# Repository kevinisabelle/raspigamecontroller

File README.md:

# RaspberryPi Bluetooth LE HID Game controller

## Reference documentation

- _HID Usage Table_: https://www.usb.org/document-library/hid-usage-tables-16
- _Device Class Definition for Human Interface Devices (HID)_: https://www.usb.org/document-library/device-class-definition-hid-111
- _HID over GATT Profile 1.0_: https://www.bluetooth.com/specifications/specs/hid-over-gatt-profile-1-0/
- _Bluez dbus interfaces_: https://github.com/bluez/bluez/tree/master/doc

## Current Issues:

- Reconnection not working automatically
- The number of axies also seems to be limited.

## Setup

### Install python and bluez

```bash
#sudo apt get py3-setuptools
sudo apt update && sudo apt upgrade -y
sudo apt install libbluetooth-dev

# Blutooth
sudo systemctl enable bluetooth
sudo systemctl start bluetooth
```

### Enable Spi0 and Spi1

- Run the raspi-config app and enable Interface Spi.
- Then modify /boot/firmware/config.txt
- Add these if not present:

```
dtparam=spi=on
dtoverlay=spi1-3cs
```

- Reboot

### Setup bluez service parameters

```bash
sudo nano /lib/systemd/system/bluetooth.service

# Modify the exec start
ExecStart=/usr/libexec/bluetooth/bluetoothd -E --noplugin=*

# Save the file and restart bluetooth

sudo systemctl daemon-reload
sudo systemctl restart bluetooth
```

### Generating the Hid Report Map and Payload Interface

In the HidTools folder, use the HidReportMapCreator program.

- Create a copy of the KiGPSimple.cs class and name it as you like
- Modify the Program.cs and use the new class to create the device reference
- Run the program
- Copy the python code from the output in the python/GamepadValues.py file
- Modify the python/UpdaterService.py and adapt the \_update_gamepad_controls according to the generated GamepadValues1 class

## Running

### Start the program

- Copy the content of the python folder on the Pi
- Run with

```bash
sudo python3 App.py
```

- Once the program is properly started, you can connect it to Windows using the Bluetooth configuration like any device.
- Once the device is bonded in Windows, you can open the "Set up USB controller" to display connected Gamepads.

## Debugging

### Using dbus-tool

Use dbus-tool to check Bluez is connecting with the program properly:

```

sudo dbus-monitor --system

```

### Using Wireshark

Use Wireshark on Windows to inspect the GATT services packets.

- Start a session using Pcap2
- Filter out protocol USB

```

!(\_ws.col.protocol == "USB")

```

- Or you can filter in the proper services:

```

(\_ws.col.protocol == "ATT" || \_ws.col.protocol == "SDP" || \_ws.col.protocol == "SMP" || \_ws.col.protocol == "GAP" || \_ws.col.protocol == "GATT" || \_ws.col.protocol == "HCI_EVT")

```

### Using Hid Explorer

You can also use this great online tool (which runs in the browser): https://nondebug.github.io/webhid-explorer/ . Using this tool you can connect to the recognized HID devices and see their definition and notifications.

## Hid Creator output example:

```
Hid Report Map and Payload interface creator
---------------------------------------------------

Notes:
-------
1. This tool is used to generate a report map and payload for a HID device.
2. The report map is a list of instructions that the device uses to send data to the host.
3. It will generate the Python class code for the report payload to use in the python part of this project.

---------------------
Report Map Descriptor
---------------------

0x05, 0x01      # Usage Page (Generic Desktop Controls)
0x09, 0x05      # Usage (Gamepad)
0xA1, 0x01      # Collection (Application)
0x85, 0x01      # Report ID 1
0x05, 0x09      # Usage Page (Button)
0x19, 0x01      # Usage Minimum (1)
0x29, 0x08      # Usage Maximum (8)
0x15, 0x00      # Logical Minimum (0)
0x25, 0x01      # Logical Maximum (1)
0x75, 0x01      # Report Size (1)
0x95, 0x08      # Report Count (8)
0x81, 0x02      # Input (00000010)
0x05, 0x01      # Usage Page (Generic Desktop Controls)
0x09, 0x36      # Usage (Slider)
0x19, 0x01      # Usage Minimum (1)
0x29, 0x01      # Usage Maximum (1)
0x15, 0x00      # Logical Minimum (0)
0x25, 0xFF      # Logical Maximum (255)
0x75, 0x08      # Report Size (8)
0x95, 0x01      # Report Count (1)
0x81, 0x02      # Input (00000010)
0x05, 0x01      # Usage Page (Generic Desktop Controls)
0x09, 0x36      # Usage (Slider)
0x19, 0x01      # Usage Minimum (1)
0x29, 0x01      # Usage Maximum (1)
0x15, 0x00      # Logical Minimum (0)
0x25, 0xFF      # Logical Maximum (255)
0x75, 0x08      # Report Size (8)
0x95, 0x01      # Report Count (1)
0x81, 0x02      # Input (00000010)
0x05, 0x01      # Usage Page (Generic Desktop Controls)
0x09, 0x36      # Usage (Slider)
0x19, 0x01      # Usage Minimum (1)
0x29, 0x01      # Usage Maximum (1)
0x15, 0x00      # Logical Minimum (0)
0x25, 0xFF      # Logical Maximum (255)
0x75, 0x08      # Report Size (8)
0x95, 0x01      # Report Count (1)
0x81, 0x02      # Input (00000010)
0xC0    # End Collection

----------------------
Report Payload Example
----------------------

Btn1 #1 (1 bits) Unspecified
Btn1 #2 (1 bits) Unspecified
Btn1 #3 (1 bits) Unspecified
Btn1 #4 (1 bits) Unspecified
Btn1 #5 (1 bits) Unspecified
Btn1 #6 (1 bits) Unspecified
Btn1 #7 (1 bits) Unspecified
Btn1 #8 (1 bits) Unspecified
Slider #1 (8 bits) Slider
Slider2 #1 (8 bits) Slider
Slider3 #1 (8 bits) Slider

----------------------------------
Report Payload Example (Formatted)
----------------------------------

BBBBBBBB SSSSSSSS SSSSSSSS SSSSSSSS
12345678 11111111 11111111 11111111

------------
Python class
------------

class GamepadValues1:
    def __init__(self, Btn10=0, Btn11=0, Btn12=0, Btn13=0, Btn14=0, Btn15=0, Btn16=0, Btn17=0, Slider0=0, Slider20=0, Slider30=0):
        self.Btn10 = Btn10 & 0x1
        self.Btn11 = Btn11 & 0x1
        self.Btn12 = Btn12 & 0x1
        self.Btn13 = Btn13 & 0x1
        self.Btn14 = Btn14 & 0x1
        self.Btn15 = Btn15 & 0x1
        self.Btn16 = Btn16 & 0x1
        self.Btn17 = Btn17 & 0x1
        self.Slider0 = Slider0 & 0xFF
        self.Slider20 = Slider20 & 0xFF
        self.Slider30 = Slider30 & 0xFF

    def set_Btn10(self, value):
        self.Btn10 = value & 0x1

    def set_Btn11(self, value):
        self.Btn11 = value & 0x1

    def set_Btn12(self, value):
        self.Btn12 = value & 0x1

    def set_Btn13(self, value):
        self.Btn13 = value & 0x1

    def set_Btn14(self, value):
        self.Btn14 = value & 0x1

    def set_Btn15(self, value):
        self.Btn15 = value & 0x1

    def set_Btn16(self, value):
        self.Btn16 = value & 0x1

    def set_Btn17(self, value):
        self.Btn17 = value & 0x1

    def set_Slider0(self, value):
        self.Slider0 = value & 0xFF

    def set_Slider20(self, value):
        self.Slider20 = value & 0xFF

    def set_Slider30(self, value):
        self.Slider30 = value & 0xFF

    def get_report(self):
        total = 0
        total = (total << 1) | self.Btn10
        total = (total << 1) | self.Btn11
        total = (total << 1) | self.Btn12
        total = (total << 1) | self.Btn13
        total = (total << 1) | self.Btn14
        total = (total << 1) | self.Btn15
        total = (total << 1) | self.Btn16
        total = (total << 1) | self.Btn17
        total = (total << 8) | self.Slider0
        total = (total << 8) | self.Slider20
        total = (total << 8) | self.Slider30
        result = total.to_bytes(4, byteorder='big')
        return bytes([0x01] + list(result))

    def get_report_map(self):
        return bytes([
            0x05, 0x01,   # Usage Page (Generic Desktop Controls)
            0x09, 0x05,   # Usage (Gamepad)
            0xA1, 0x01,   # Collection (Application)
            0x85, 0x01,   # Report ID 1
            0x05, 0x09,   # Usage Page (Button)
            0x19, 0x01,   # Usage Minimum (1)
            0x29, 0x08,   # Usage Maximum (8)
            0x15, 0x00,   # Logical Minimum (0)
            0x25, 0x01,   # Logical Maximum (1)
            0x75, 0x01,   # Report Size (1)
            0x95, 0x08,   # Report Count (8)
            0x81, 0x02,   # Input (00000010)
            0x05, 0x01,   # Usage Page (Generic Desktop Controls)
            0x09, 0x36,   # Usage (Slider)
            0x19, 0x01,   # Usage Minimum (1)
            0x29, 0x01,   # Usage Maximum (1)
            0x15, 0x00,   # Logical Minimum (0)
            0x25, 0xFF,   # Logical Maximum (255)
            0x75, 0x08,   # Report Size (8)
            0x95, 0x01,   # Report Count (1)
            0x81, 0x02,   # Input (00000010)
            0x05, 0x01,   # Usage Page (Generic Desktop Controls)
            0x09, 0x36,   # Usage (Slider)
            0x19, 0x01,   # Usage Minimum (1)
            0x29, 0x01,   # Usage Maximum (1)
            0x15, 0x00,   # Logical Minimum (0)
            0x25, 0xFF,   # Logical Maximum (255)
            0x75, 0x08,   # Report Size (8)
            0x95, 0x01,   # Report Count (1)
            0x81, 0x02,   # Input (00000010)
            0x05, 0x01,   # Usage Page (Generic Desktop Controls)
            0x09, 0x36,   # Usage (Slider)
            0x19, 0x01,   # Usage Minimum (1)
            0x29, 0x01,   # Usage Maximum (1)
            0x15, 0x00,   # Logical Minimum (0)
            0x25, 0xFF,   # Logical Maximum (255)
            0x75, 0x08,   # Report Size (8)
            0x95, 0x01,   # Report Count (1)
            0x81, 0x02,   # Input (00000010)
            0xC0,   # End Collection
        ])

```

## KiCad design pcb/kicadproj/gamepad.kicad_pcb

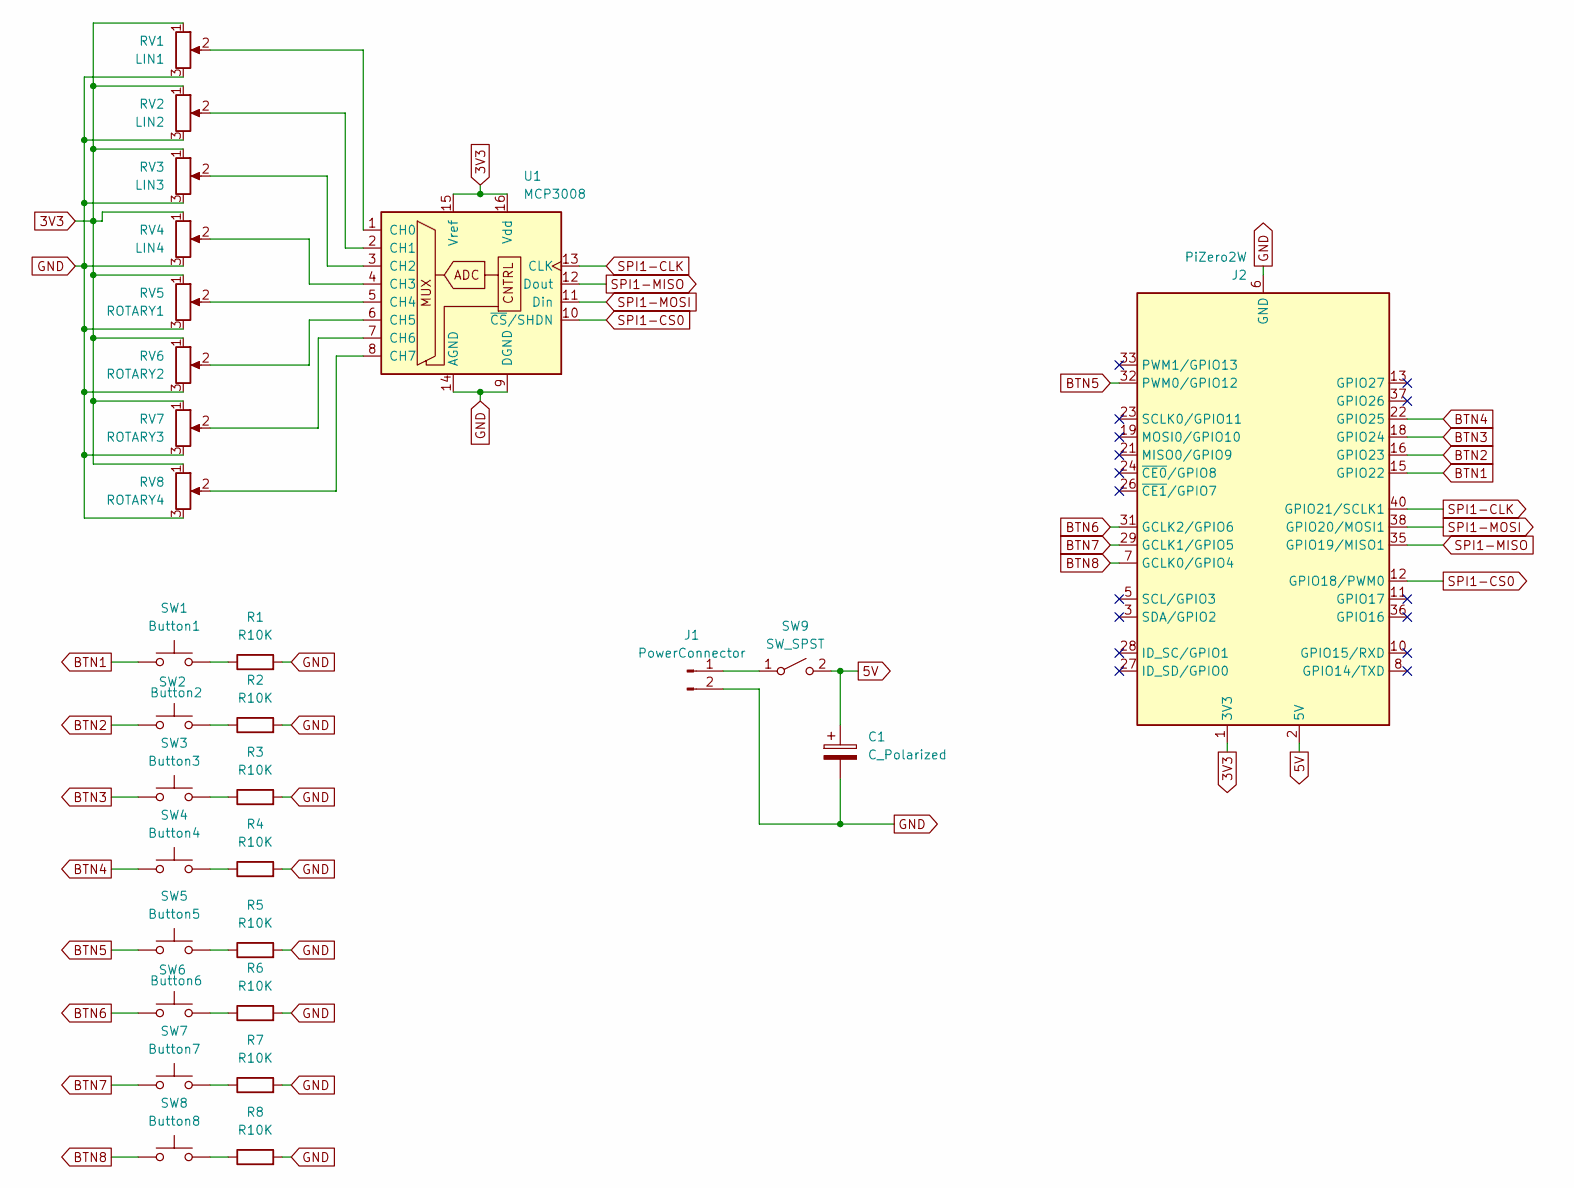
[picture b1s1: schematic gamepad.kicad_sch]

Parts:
C1: C_Polarized; CP_Radial_D4.0mm_P2.00mm
J1: PowerConnector; PinHeader_1x02_P2.54mm_Vertical
J2: PiZero2W; PinSocket_2x20_P2.54mm_Vertical
R1, R2, R3, R4, R5, R6, R7, R8: R10K; R_1206_3216Metric_Pad1.30x1.75mm_HandSolder
RV1: LIN1; Potentiometer_Bourns_PTA6043_Single_Slide
RV2: LIN2; Potentiometer_Bourns_PTA6043_Single_Slide
RV3: LIN3; Potentiometer_Bourns_PTA6043_Single_Slide
RV4: LIN4; Potentiometer_Bourns_PTA6043_Single_Slide
RV5: ROTARY1; Potentiometer_Bourns_PTV09A-1_Single_Vertical
RV6: ROTARY2; Potentiometer_Bourns_PTV09A-1_Single_Vertical
RV7: ROTARY3; Potentiometer_Bourns_PTV09A-1_Single_Vertical
RV8: ROTARY4; Potentiometer_Bourns_PTV09A-1_Single_Vertical
SW1: Button1; SW_SPST_Omron_B3F-40xx
SW2: Button2; SW_SPST_Omron_B3F-40xx
SW3: Button3; SW_SPST_Omron_B3F-40xx
SW4: Button4; SW_SPST_Omron_B3F-40xx
SW5: Button5; SW_SPST_Omron_B3F-40xx
SW6: Button6; SW_SPST_Omron_B3F-40xx
SW7: Button7; SW_SPST_Omron_B3F-40xx
SW8: Button8; SW_SPST_Omron_B3F-40xx
SW9: SW_SPST; SW_DIP_SPSTx01_Slide_9.78x4.72mm_W7.62mm_P2.54mm
U1: MCP3008; CERDIP-16_W7.62mm_SideBrazed_Socket

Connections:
3V3: J2.1 (3V3), J2.17 (3V3), RV1.1, RV2.1, RV3.1, RV4.1, RV5.1, RV6.1, RV7.1, RV8.1, U1.15 (Vref), U1.16 (Vdd)
5V: C1.1, J2.2 (5V), J2.4 (5V), SW9.2 (B)
BTN1: J2.15 (GPIO22), SW1.1
BTN2: J2.16 (GPIO23), SW2.1
BTN3: J2.18 (GPIO24), SW3.1
BTN4: J2.22 (GPIO25), SW4.1
BTN5: J2.32 (PWM0/GPIO12), SW5.1
BTN6: J2.31 (GCLK2/GPIO6), SW6.1
BTN7: J2.29 (GCLK1/GPIO5), SW7.1
BTN8: J2.7 (GCLK0/GPIO4), SW8.1
GND: C1.2, J1.2, J2.6 (GND), J2.9 (GND), J2.14 (GND), J2.20 (GND), J2.25 (GND), J2.30 (GND), J2.34 (GND), J2.39 (GND), R1.2, R2.2, R3.2, R4.2, R5.2, R6.2, R7.2, R8.2, RV1.3, RV2.3, RV3.3, RV4.3, RV5.3, RV6.3, RV7.3, RV8.3, U1.9 (DGND), U1.14 (AGND)
unnamed: J1.1, SW9.1 (A)
unnamed: R1.1, SW1.2
unnamed: R2.1, SW2.2
unnamed: R3.1, SW3.2
unnamed: R4.1, SW4.2
unnamed: R5.1, SW5.2
unnamed: R6.1, SW6.2
unnamed: R7.1, SW7.2
unnamed: R8.1, SW8.2
unnamed: RV1.2, U1.1 (CH0)
unnamed: RV2.2, U1.2 (CH1)
unnamed: RV3.2, U1.3 (CH2)
unnamed: RV4.2, U1.4 (CH3)
unnamed: RV5.2, U1.5 (CH4)
unnamed: RV6.2, U1.6 (CH5)
unnamed: RV7.2, U1.7 (CH6)
unnamed: RV8.2, U1.8 (CH7)
SPI1-CLK: J2.40 (GPIO21/SCLK1), U1.13 (CLK)
SPI1-CS0: J2.12 (GPIO18/PWM0), U1.10 (~CS/SHDN)
SPI1-MISO: J2.35 (GPIO19/MISO1), U1.12 (Dout)
SPI1-MOSI: J2.38 (GPIO20/MOSI1), U1.11 (Din)

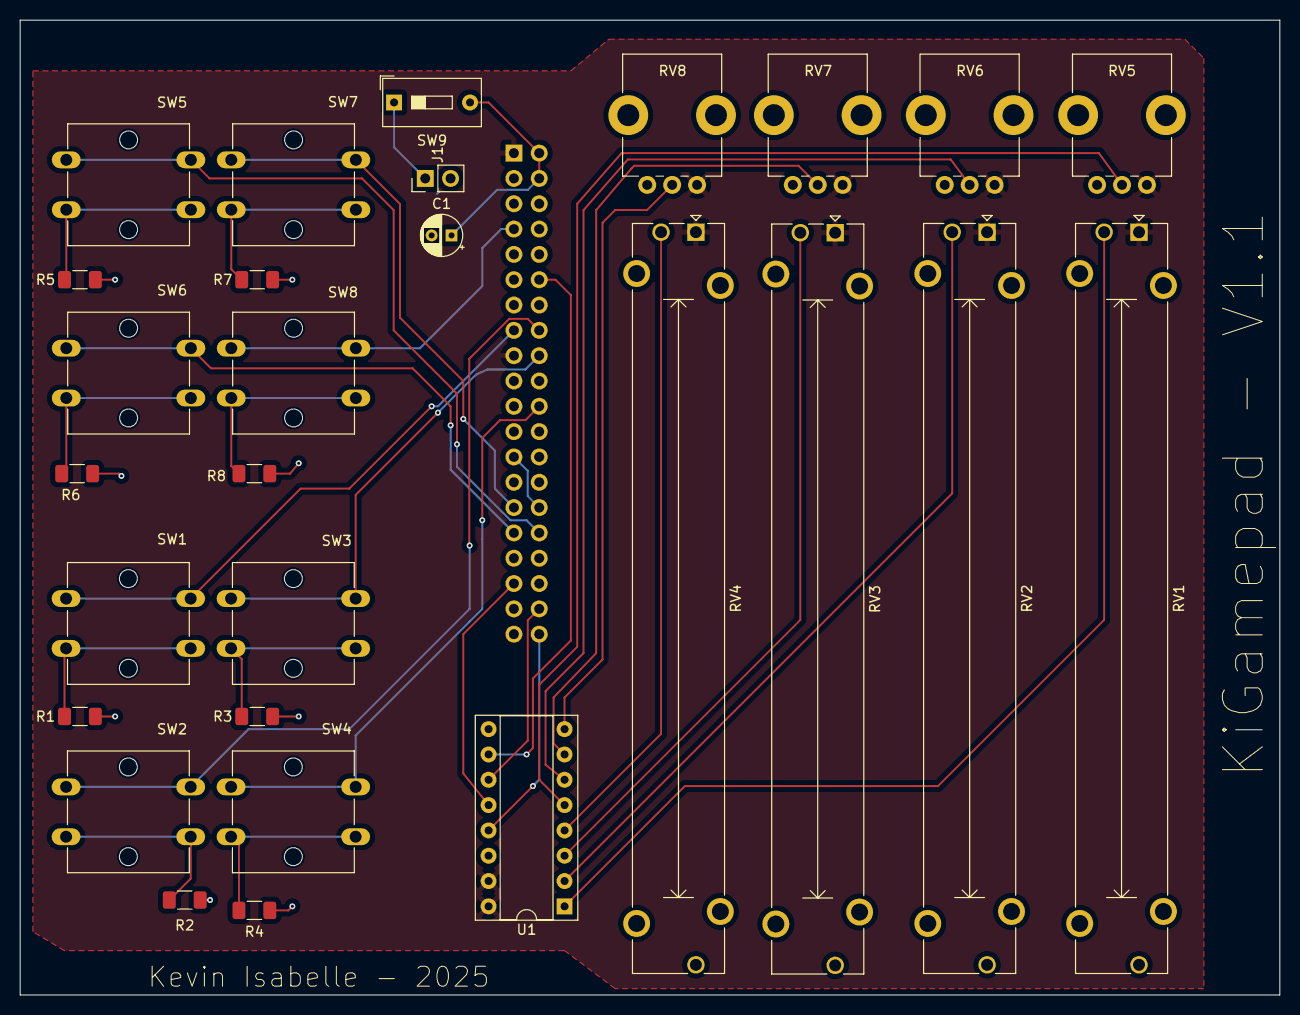
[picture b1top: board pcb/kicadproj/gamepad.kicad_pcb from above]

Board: 2 copper layers, 126.4 x 97.8 mm, 29 parts (1 on the bottom side), 32 nets.

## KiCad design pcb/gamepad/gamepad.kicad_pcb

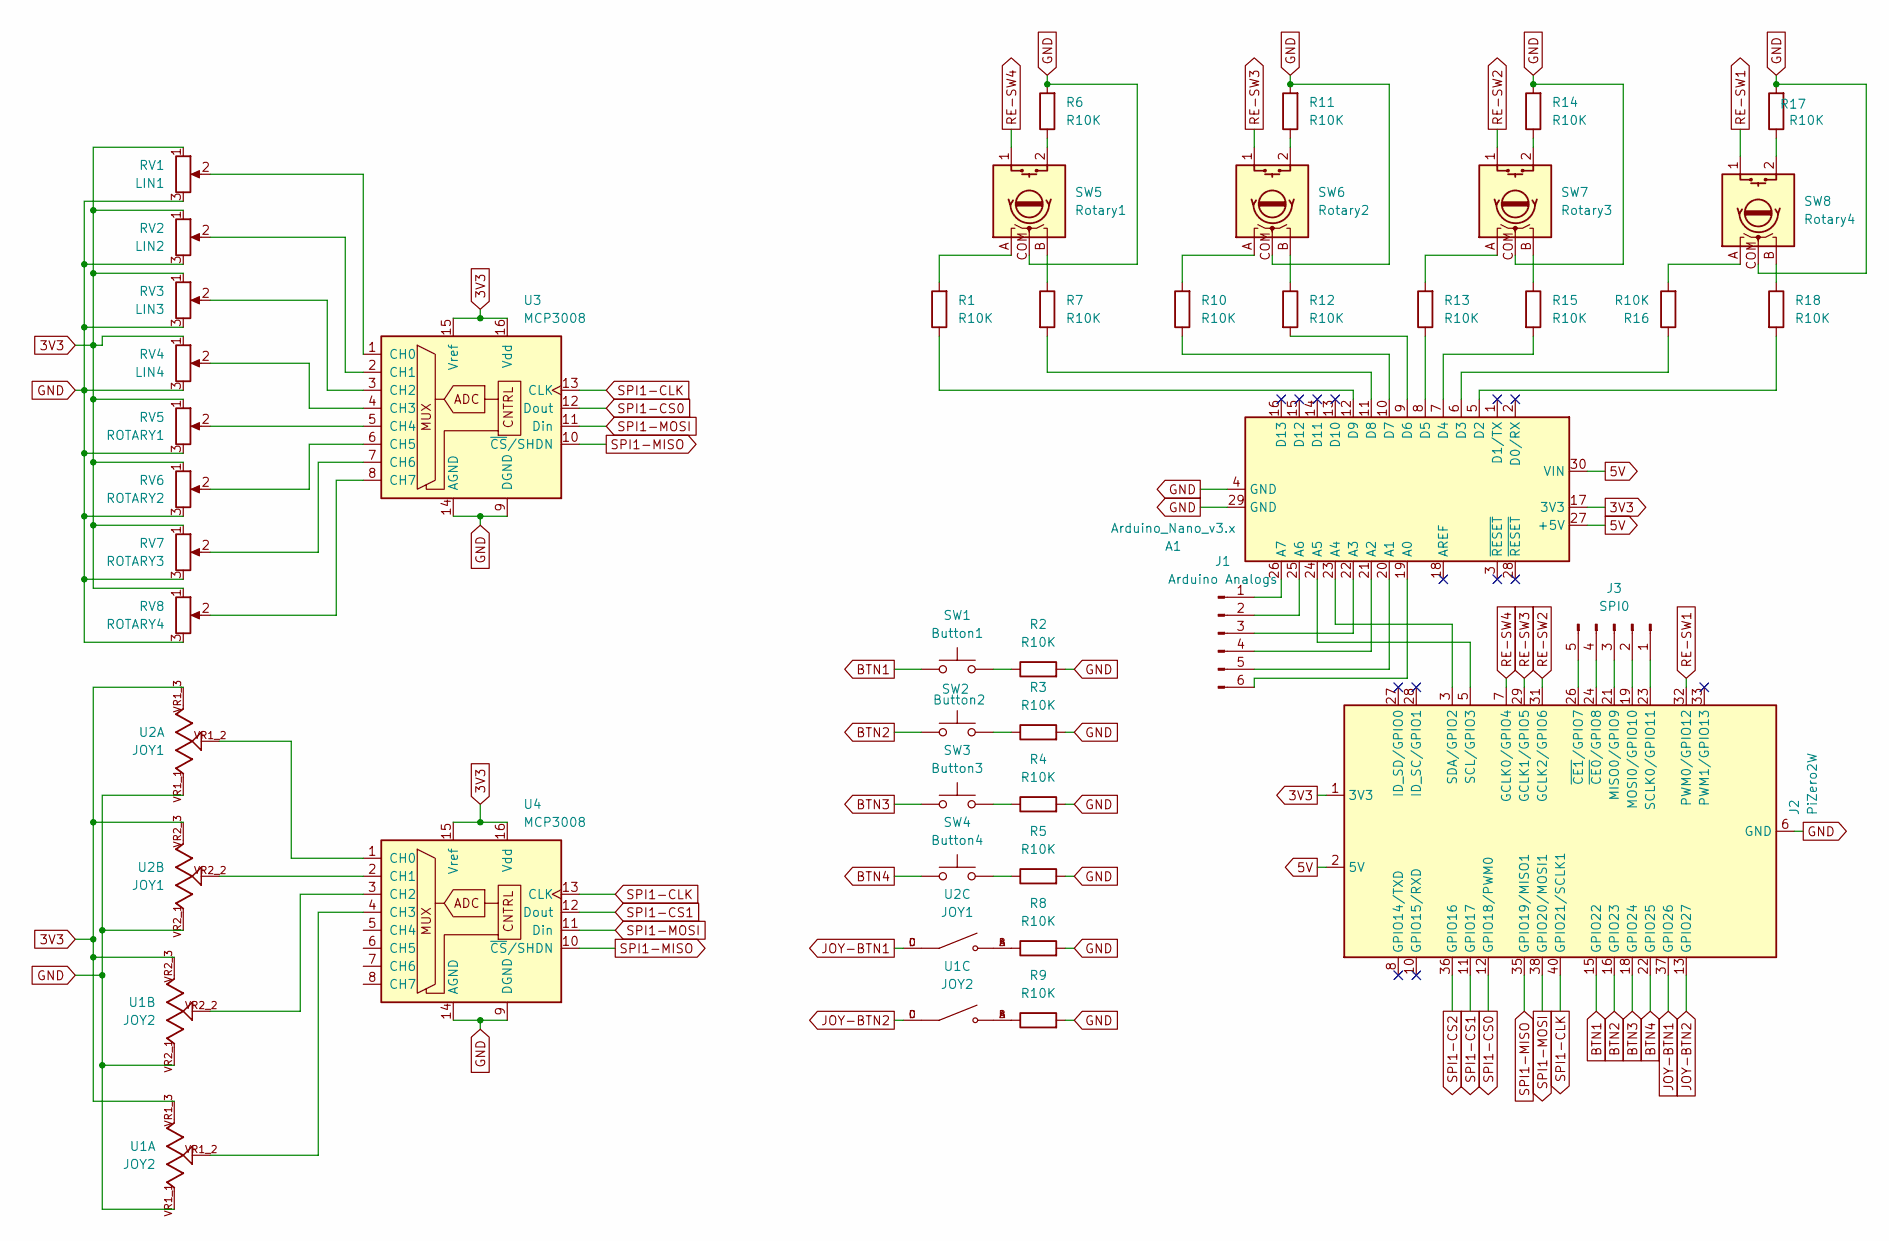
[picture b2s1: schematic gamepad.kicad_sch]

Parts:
A1: Arduino_Nano_v3.x; Arduino_Nano
J1: Arduino Analogs; PinSocket_1x05_P2.54mm_Vertical
J2: PiZero2W; PinSocket_2x20_P2.54mm_Vertical
J3: SPI0; PinSocket_1x05_P2.54mm_Vertical
R1, R2, R3, R4, R5, R6, R7, R8, R9, R10, R11, R12, R13, R14, R15, R16, R17, R18: R10K; R_1206_3216Metric_Pad1.30x1.75mm_HandSolder
RV1: LIN1; Potentiometer_Bourns_PTA6043_Single_Slide
RV2: LIN2; Potentiometer_Bourns_PTA6043_Single_Slide
RV3: LIN3; Potentiometer_Bourns_PTA4543_Single_Slide
RV4: LIN4; Potentiometer_Bourns_PTA4543_Single_Slide
RV5: ROTARY1; Potentiometer_Bourns_PTV09A-1_Single_Vertical
RV6: ROTARY2; Potentiometer_Bourns_PTV09A-1_Single_Vertical
RV7: ROTARY3; Potentiometer_Bourns_PTV09A-1_Single_Vertical
RV8: ROTARY4; Potentiometer_Bourns_PTV09A-1_Single_Vertical
SW1: Button1; SW_SPST_Omron_B3F-40xx
SW2: Button2; SW_SPST_Omron_B3F-40xx
SW3: Button3; SW_SPST_Omron_B3F-40xx
SW4: Button4; SW_SPST_Omron_B3F-40xx
SW5: Rotary1; PEC11R-4215F-S0024
SW6: Rotary2; PEC11R-4215F-S0024
SW7: Rotary3; PEC11R-4215F-S0024
SW8: Rotary4; PEC11R-4215F-S0024
U1: JOY2; CNK_THB001P; PARTREV 27 Jan 22; DigiKey_Part_Number 108-THB001P-ND
U2: JOY1; CNK_THB001P; PARTREV 27 Jan 22; DigiKey_Part_Number 108-THB001P-ND
U3, U4: MCP3008; CERDIP-16_W7.62mm_SideBrazed_Socket

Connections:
3V3: A1.17 (3V3), J2.1 (3V3), J2.17 (3V3), RV1.1, RV2.1, RV3.1, RV4.1, RV5.1, RV6.1, RV7.1, RV8.1, U1.VR1_3, U1.VR2_3, U2.VR1_3, U2.VR2_3, U3.15 (Vref), U3.16 (Vdd), U4.15 (Vref), U4.16 (Vdd)
5V: A1.27 (+5V), A1.30 (VIN), J2.2 (5V), J2.4 (5V)
BTN1: J2.15 (GPIO22), SW1.1
BTN2: J2.16 (GPIO23), SW2.1
BTN3: J2.18 (GPIO24), SW3.1
BTN4: J2.22 (GPIO25), SW4.1
GND: A1.4 (GND), A1.29 (GND), J2.6 (GND), J2.9 (GND), J2.14 (GND), J2.20 (GND), J2.25 (GND), J2.30 (GND), J2.34 (GND), J2.39 (GND), R2.2, R3.2, R4.2, R5.2, R6.2, R8.2, R9.2, R11.2, R14.2, R17.2, RV1.3, RV2.3, RV3.3, RV4.3, RV5.3, RV6.3, RV7.3, RV8.3, SW5.COM (Com), SW6.COM (Com), SW7.COM (Com), SW8.COM (Com), U1.VR1_1, U1.VR2_1, U2.VR1_1, U2.VR2_1, U3.9 (DGND), U3.14 (AGND), U4.9 (DGND), U4.14 (AGND)
JOY-BTN1: J2.37 (GPIO26), U2.C, U2.D
JOY-BTN2: J2.13 (GPIO27), U1.C, U1.D
unnamed: A1.19 (A0), J1.6
unnamed: A1.20 (A1), J1.5
unnamed: A1.21 (A2), J1.4
unnamed: A1.22 (A3), J1.3
unnamed: A1.23 (A4), J2.3 (SDA/GPIO2)
unnamed: A1.24 (A5), J2.5 (SCL/GPIO3)
unnamed: A1.25 (A6), J1.2
unnamed: A1.26 (A7), J1.1
unnamed: A1.5 (D2), R18.2
unnamed: A1.6 (D3), R16.1
unnamed: A1.7 (D4), R15.2
unnamed: A1.8 (D5), R13.1
unnamed: A1.9 (D6), R12.2
unnamed: A1.10 (D7), R10.1
unnamed: A1.11 (D8), R7.2
unnamed: A1.12 (D9), R1.1
unnamed: J2.21 (MISO0/GPIO9), J3.3
unnamed: J2.19 (MOSI0/GPIO10), J3.2
unnamed: J2.23 (SCLK0/GPIO11), J3.1
unnamed: J2.24 (~CE0/GPIO8), J3.4
unnamed: J2.26 (~CE1/GPIO7), J3.5
unnamed: R1.2, SW5.A
unnamed: R2.1, SW1.2
unnamed: R3.1, SW2.2
unnamed: R4.1, SW3.2
unnamed: R5.1, SW4.2
unnamed: R6.1, SW5.2
unnamed: R7.1, SW5.B
unnamed: R8.1, U2.A, U2.B
unnamed: R9.1, U1.A, U1.B
unnamed: R10.2, SW6.A
unnamed: R11.1, SW6.2
unnamed: R12.1, SW6.B
unnamed: R13.2, SW7.A
unnamed: R14.1, SW7.2
unnamed: R15.1, SW7.B
unnamed: R16.2, SW8.A
unnamed: R17.1, SW8.2
unnamed: R18.1, SW8.B
unnamed: RV1.2, U3.1 (CH0)
unnamed: RV2.2, U3.2 (CH1)
unnamed: RV3.2, U3.3 (CH2)
unnamed: RV4.2, U3.4 (CH3)
unnamed: RV5.2, U3.5 (CH4)
unnamed: RV6.2, U3.6 (CH5)
unnamed: RV7.2, U3.7 (CH6)
unnamed: RV8.2, U3.8 (CH7)
unnamed: U2.VR1_2, U4.1 (CH0)
unnamed: U2.VR2_2, U4.2 (CH1)
unnamed: U1.VR2_2, U4.3 (CH2)
unnamed: U1.VR1_2, U4.4 (CH3)
RE-SW1: J2.32 (PWM0/GPIO12), SW8.1
RE-SW2: J2.31 (GCLK2/GPIO6), SW7.1
RE-SW3: J2.29 (GCLK1/GPIO5), SW6.1
RE-SW4: J2.7 (GCLK0/GPIO4), SW5.1
SPI1-CLK: J2.40 (GPIO21/SCLK1), U3.13 (CLK), U4.13 (CLK)
SPI1-CS0: J2.12 (GPIO18/PWM0), U3.12 (Dout)
SPI1-CS1: J2.11 (GPIO17), U4.12 (Dout)
SPI1-CS2: J2.36 (GPIO16)
SPI1-MISO: J2.35 (GPIO19/MISO1), U3.10 (~CS/SHDN), U4.10 (~CS/SHDN)
SPI1-MOSI: J2.38 (GPIO20/MOSI1), U3.11 (Din), U4.11 (Din)

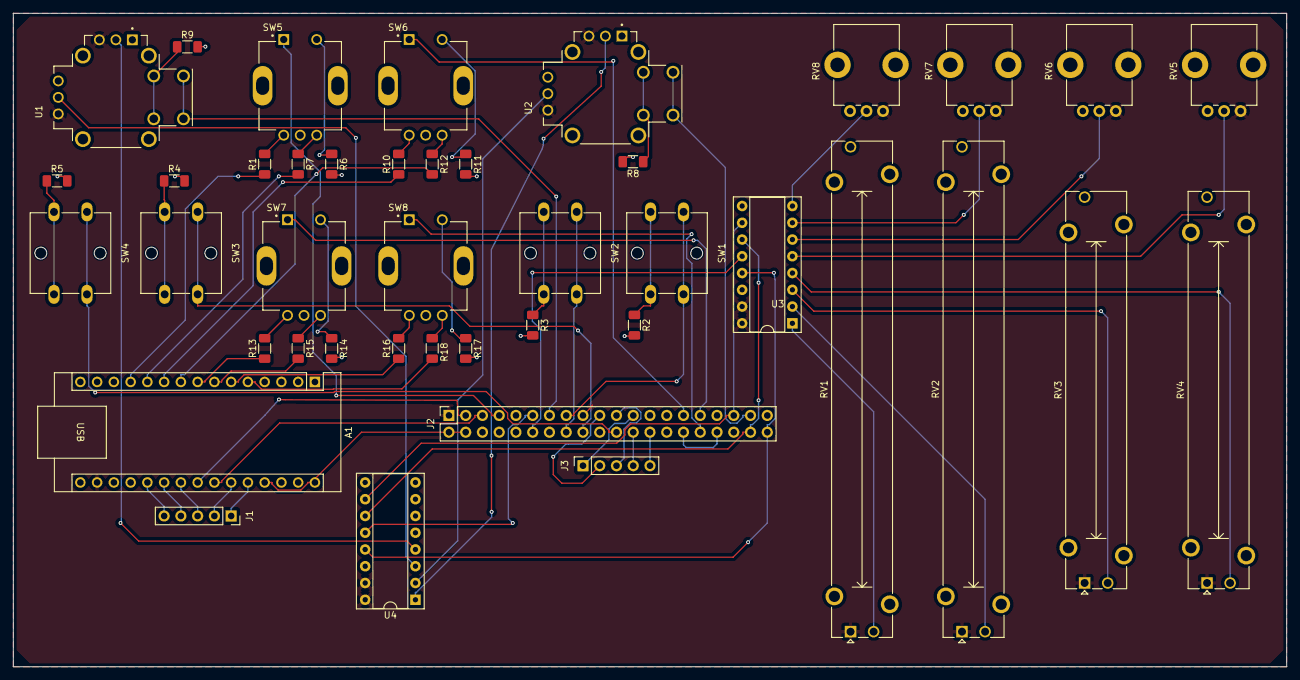
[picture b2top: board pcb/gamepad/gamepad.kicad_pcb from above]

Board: 2 copper layers, 193.0 x 99.1 mm, 42 parts (0 on the bottom side), 68 nets.

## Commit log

2025-01-25 wip lcd
2025-01-29 wip pcb
2025-02-16 eureka! mostly...
2025-02-18 wip ça marche
2025-02-18 Rename constants.py to Constants.py
2025-03-05 Box, Pcb, fixes
2025-03-06 wip c
2025-03-12 wip Rust
2025-03-26 wip rust, removed dead c and c++ code.
2025-03-27 wip rust, almost done!
2025-03-28 wip rust, fixed hardware
2025-03-28 cleanup
2025-03-29 Rust implementation is working.
2025-03-29 Added hid gamepad windows limitation research doc
2025-03-29 Rust todo list update
